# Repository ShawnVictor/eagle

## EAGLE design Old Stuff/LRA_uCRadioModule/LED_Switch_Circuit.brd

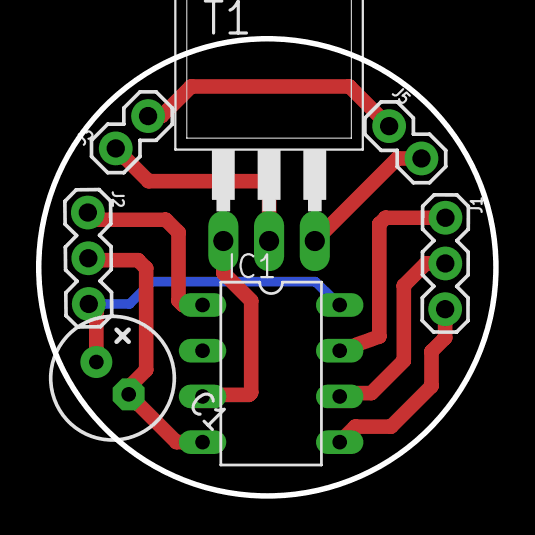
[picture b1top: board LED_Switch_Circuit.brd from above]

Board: 2 copper layers, 25.4 x 25.4 mm, 7 parts (0 on the bottom side), 10 nets.

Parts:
C1: E-025X060
IC1: TINY13-20PU; DIL08
J1, J2: 1X03
J3, J5: 1X02
T1: TIP31; TO220

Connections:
5V: C1.+, IC1.8, J2.3
GND: C1.-, IC1.4, J2.2
unnamed: J5.2, T1.3
unnamed: J3.2, J5.1
unnamed: J3.1, T1.2
unnamed: IC1.3, T1.1
PIN10: IC1.1, J2.1
PIN11: IC1.5, J1.3
PIN12: IC1.6, J1.2
PIN13: IC1.7, J1.1

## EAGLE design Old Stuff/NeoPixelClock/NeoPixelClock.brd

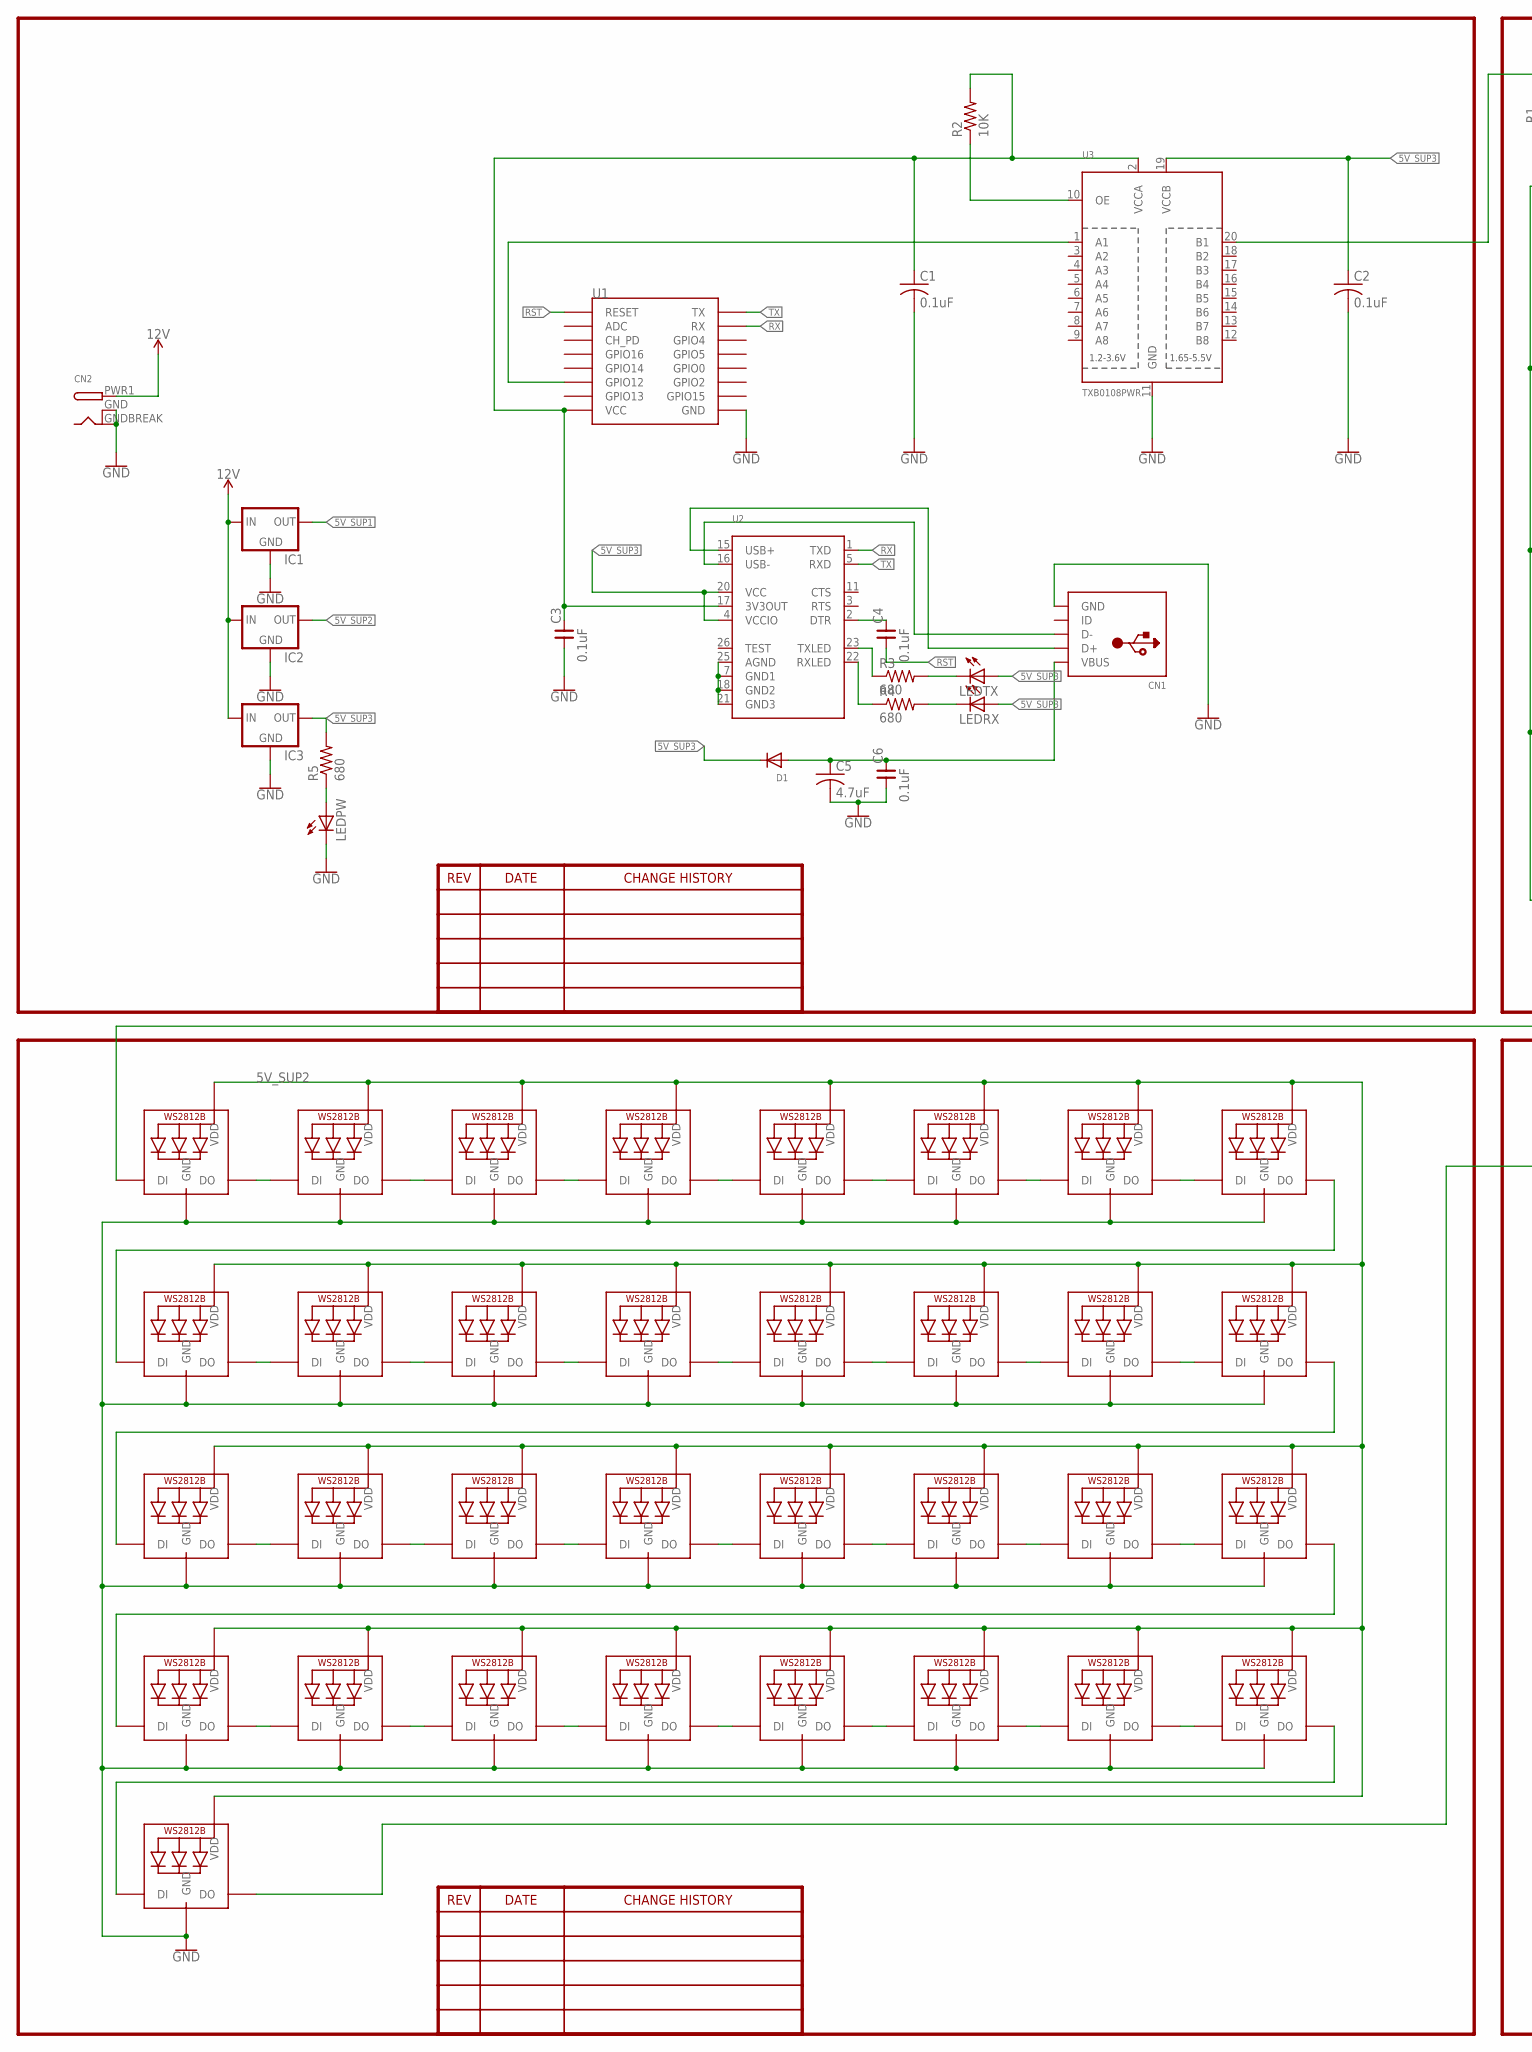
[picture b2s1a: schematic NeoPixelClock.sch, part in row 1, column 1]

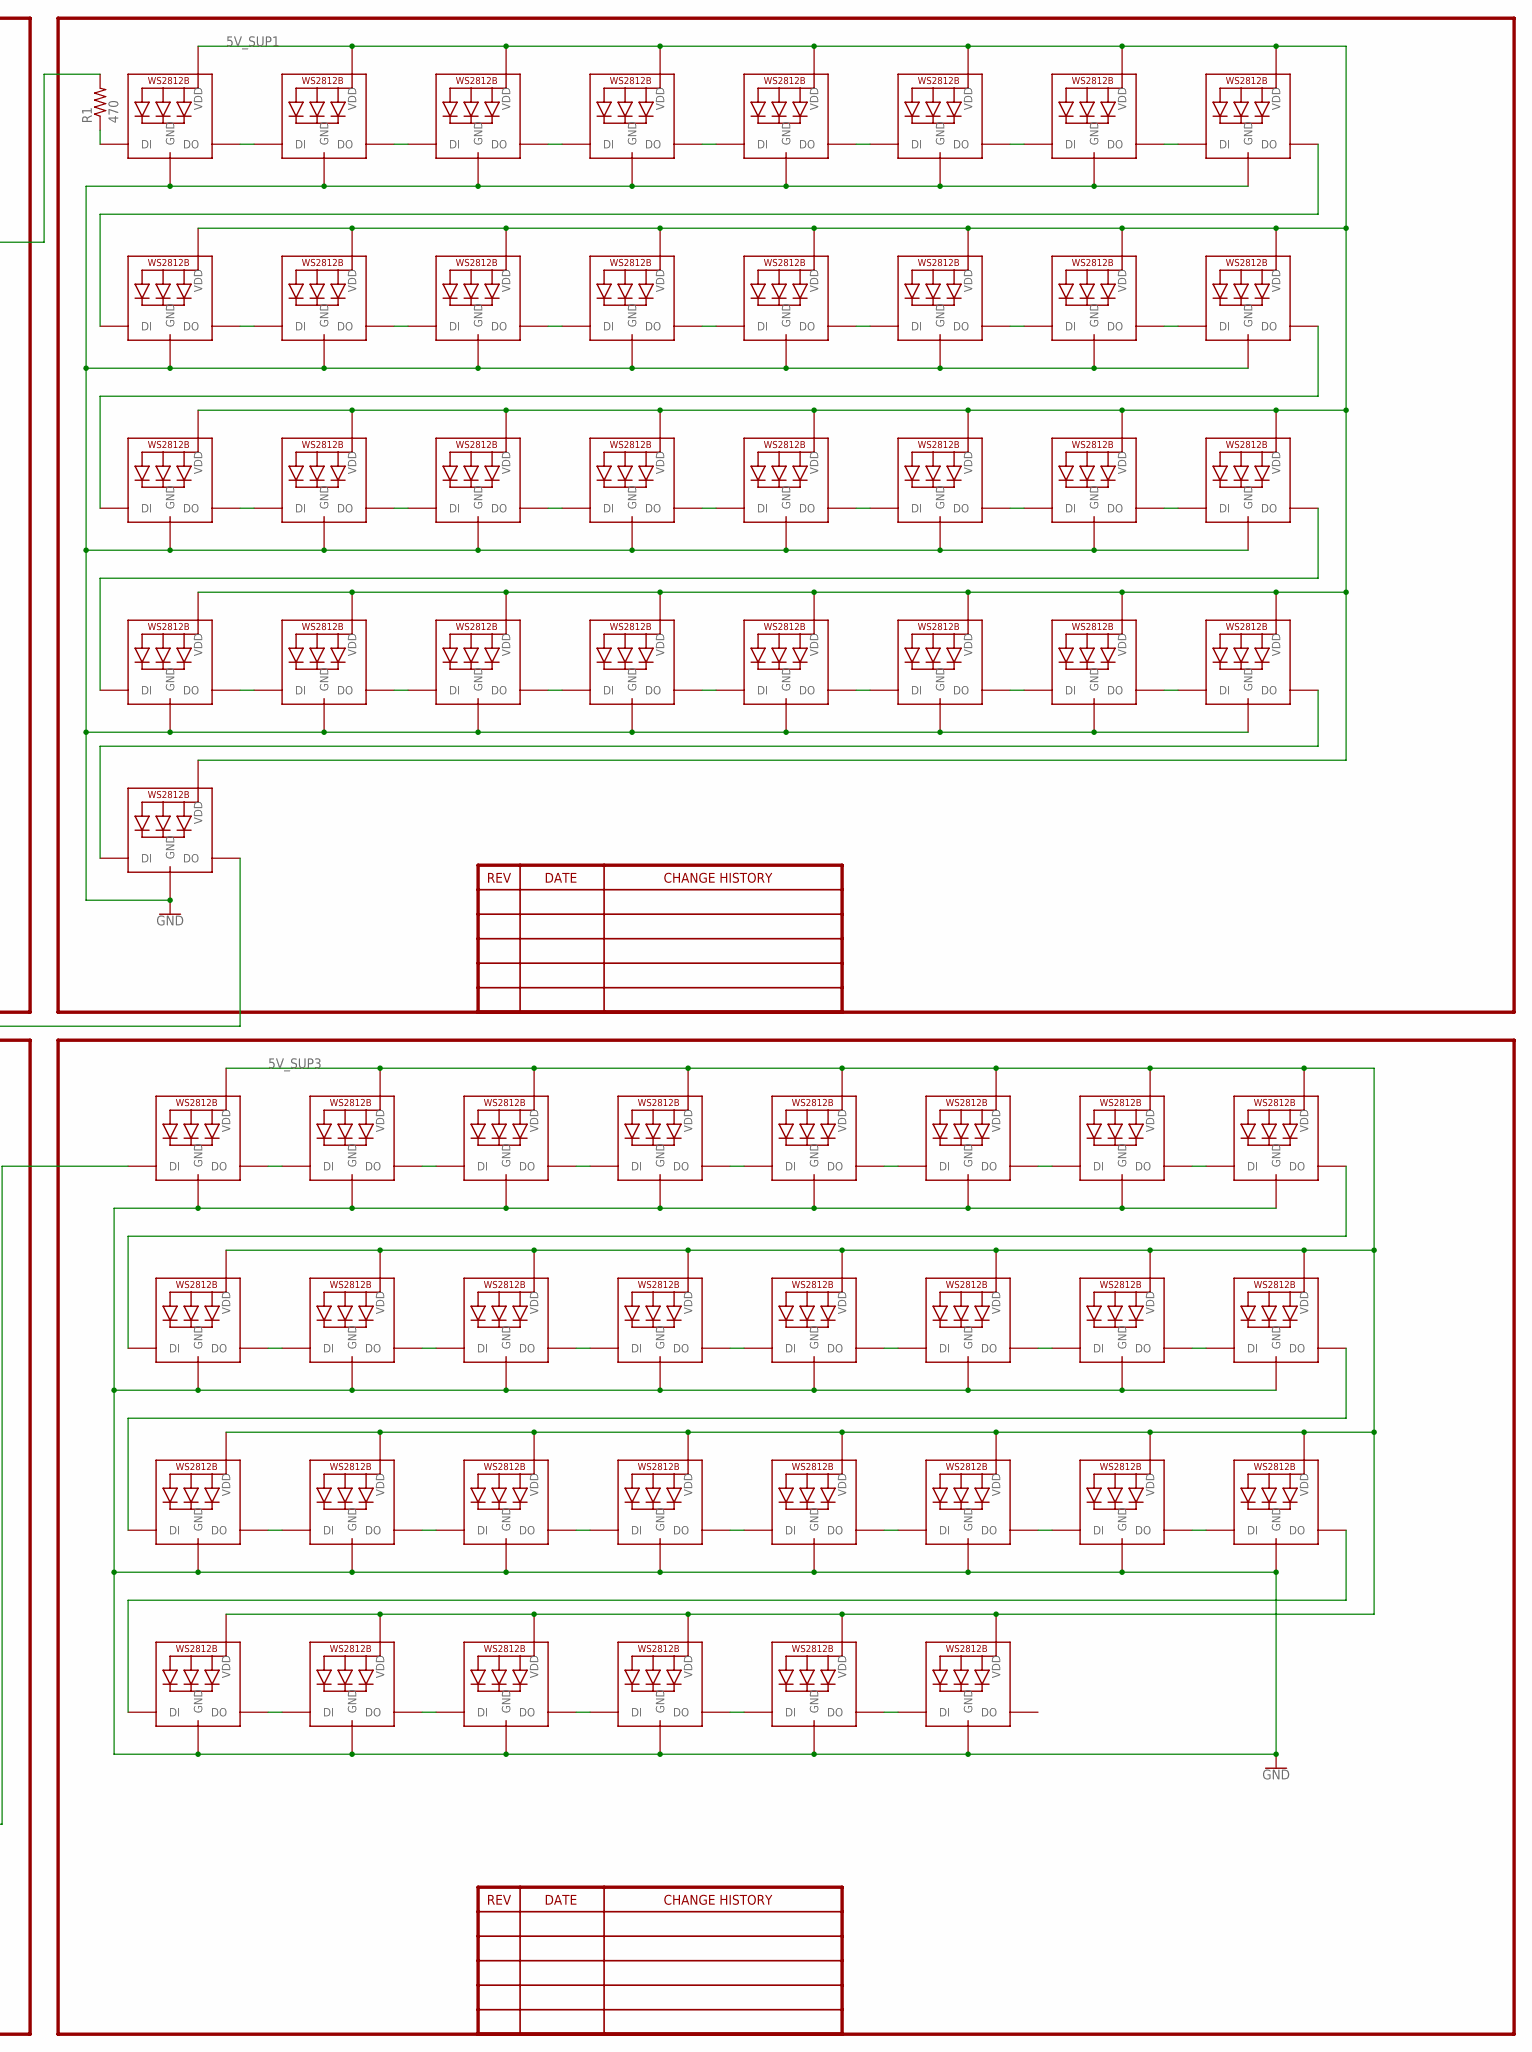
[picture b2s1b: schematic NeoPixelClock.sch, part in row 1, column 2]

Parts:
C1, C2: 0.1uF; C0805
C3, C4, C6: 0.1uF; 0805
C5: 4.7uF; C0805
CN1: USBMINIB; USB-MINIB
CN2: DCBARRELSMT; DCJACK_2MM_SMT
D1: DIODESOD-123; SOD-123
IC1, IC2, IC3: V_REG_78XXSIDE; 78XXL
LED1, LED2, LED3, LED4, LED5, LED6, LED7, LED8, LED9, LED10, LED11, LED12, LED13, LED14, LED15, LED16, LED17, LED18, LED19, LED20, LED21, LED22, LED23, LED24, LED25, LED26, LED27, LED28, LED29, LED30, LED31, LED32, LED33, LED34, LED35, LED36, LED37, LED38, LED39, LED40, LED41, LED42, LED43, LED44, LED45, LED46, LED47, LED48, LED49, LED50, LED51, LED52, LED53, LED54, LED55, LED56, LED57, LED58, LED59, LED60, LED61, LED62, LED63, LED64, LED65, LED66, LED67, LED68, LED69, LED70, LED71, LED72, LED73, LED74, LED75, LED76, LED77, LED78, LED79, LED80, LED81, LED82, LED83, LED84, LED85, LED86, LED87, LED88, LED89, LED90, LED91, LED92, LED93, LED94, LED95, LED96: WS2812B5050; WS2812B
LEDPW: LEDCHIP-LED0805; CHIP-LED0805
LEDRX: LEDCHIP-LED0805; CHIP-LED0805
LEDTX: LEDCHIP-LED0805; CHIP-LED0805
R1: 470; M0805
R2: 10K; R0805
R3, R4, R5: 680; R0805
U1: ESP12
U2: FT232RLSSOP28; SSOP28DB
U3: TXB0108PWR; TSSOP20

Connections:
3V3: C1.1, C3.2, R2.2, U1.VCC, U2.17 (3V3OUT), U3.2 (VCCA)
5V_SUP1: IC1.OUT, LED1.1-VDD (VDD), LED2.1-VDD (VDD), LED3.1-VDD (VDD), LED4.1-VDD (VDD), LED5.1-VDD (VDD), LED6.1-VDD (VDD), LED7.1-VDD (VDD), LED8.1-VDD (VDD), LED9.1-VDD (VDD), LED10.1-VDD (VDD), LED11.1-VDD (VDD), LED12.1-VDD (VDD), LED13.1-VDD (VDD), LED14.1-VDD (VDD), LED15.1-VDD (VDD), LED16.1-VDD (VDD), LED17.1-VDD (VDD), LED18.1-VDD (VDD), LED19.1-VDD (VDD), LED20.1-VDD (VDD), LED21.1-VDD (VDD), LED22.1-VDD (VDD), LED23.1-VDD (VDD), LED24.1-VDD (VDD), LED25.1-VDD (VDD), LED26.1-VDD (VDD), LED27.1-VDD (VDD), LED28.1-VDD (VDD), LED29.1-VDD (VDD), LED30.1-VDD (VDD), LED31.1-VDD (VDD), LED32.1-VDD (VDD), LED33.1-VDD (VDD)
5V_SUP2: IC2.OUT, LED34.1-VDD (VDD), LED35.1-VDD (VDD), LED36.1-VDD (VDD), LED37.1-VDD (VDD), LED38.1-VDD (VDD), LED39.1-VDD (VDD), LED40.1-VDD (VDD), LED41.1-VDD (VDD), LED42.1-VDD (VDD), LED43.1-VDD (VDD), LED44.1-VDD (VDD), LED45.1-VDD (VDD), LED46.1-VDD (VDD), LED47.1-VDD (VDD), LED48.1-VDD (VDD), LED49.1-VDD (VDD), LED50.1-VDD (VDD), LED51.1-VDD (VDD), LED52.1-VDD (VDD), LED53.1-VDD (VDD), LED54.1-VDD (VDD), LED55.1-VDD (VDD), LED56.1-VDD (VDD), LED57.1-VDD (VDD), LED58.1-VDD (VDD), LED59.1-VDD (VDD), LED60.1-VDD (VDD), LED61.1-VDD (VDD), LED62.1-VDD (VDD), LED63.1-VDD (VDD), LED64.1-VDD (VDD), LED65.1-VDD (VDD), LED66.1-VDD (VDD)
5V_SUP3: C2.1, D1.C, IC3.OUT, LED67.1-VDD (VDD), LED68.1-VDD (VDD), LED69.1-VDD (VDD), LED70.1-VDD (VDD), LED71.1-VDD (VDD), LED72.1-VDD (VDD), LED73.1-VDD (VDD), LED74.1-VDD (VDD), LED75.1-VDD (VDD), LED76.1-VDD (VDD), LED77.1-VDD (VDD), LED78.1-VDD (VDD), LED79.1-VDD (VDD), LED80.1-VDD (VDD), LED81.1-VDD (VDD), LED82.1-VDD (VDD), LED83.1-VDD (VDD), LED84.1-VDD (VDD), LED85.1-VDD (VDD), LED86.1-VDD (VDD), LED87.1-VDD (VDD), LED88.1-VDD (VDD), LED89.1-VDD (VDD), LED90.1-VDD (VDD), LED91.1-VDD (VDD), LED92.1-VDD (VDD), LED93.1-VDD (VDD), LED94.1-VDD (VDD), LED95.1-VDD (VDD), LED96.1-VDD (VDD), LEDRX.A, LEDTX.A, R5.2, U2.4 (VCCIO), U2.20 (VCC), U3.19 (VCCB)
12V: CN2.PWR1 (PWR), IC1.IN, IC2.IN, IC3.IN
GND: C1.2, C2.2, C3.1, C5.2, C6.1, CN1.GND, CN2.GND (GNDBREAK), CN2.GNDBREAK (GND), IC1.GND, IC2.GND, IC3.GND, LED1.3-GND (GND), LED2.3-GND (GND), LED3.3-GND (GND), LED4.3-GND (GND), LED5.3-GND (GND), LED6.3-GND (GND), LED7.3-GND (GND), LED8.3-GND (GND), LED9.3-GND (GND), LED10.3-GND (GND), LED11.3-GND (GND), LED12.3-GND (GND), LED13.3-GND (GND), LED14.3-GND (GND), LED15.3-GND (GND), LED16.3-GND (GND), LED17.3-GND (GND), LED18.3-GND (GND), LED19.3-GND (GND), LED20.3-GND (GND), LED21.3-GND (GND), LED22.3-GND (GND), LED23.3-GND (GND), LED24.3-GND (GND), LED25.3-GND (GND), LED26.3-GND (GND), LED27.3-GND (GND), LED28.3-GND (GND), LED29.3-GND (GND), LED30.3-GND (GND), LED31.3-GND (GND), LED32.3-GND (GND), LED33.3-GND (GND), LED34.3-GND (GND), LED35.3-GND (GND), LED36.3-GND (GND), LED37.3-GND (GND), LED38.3-GND (GND), LED39.3-GND (GND), LED40.3-GND (GND), LED41.3-GND (GND), LED42.3-GND (GND), LED43.3-GND (GND), LED44.3-GND (GND), LED45.3-GND (GND), LED46.3-GND (GND), LED47.3-GND (GND), LED48.3-GND (GND), LED49.3-GND (GND), LED50.3-GND (GND), LED51.3-GND (GND), LED52.3-GND (GND), LED53.3-GND (GND), LED54.3-GND (GND), LED55.3-GND (GND), LED56.3-GND (GND), LED57.3-GND (GND), LED58.3-GND (GND), LED59.3-GND (GND), LED60.3-GND (GND), LED61.3-GND (GND), LED62.3-GND (GND), LED63.3-GND (GND), LED64.3-GND (GND), LED65.3-GND (GND), LED66.3-GND (GND), LED67.3-GND (GND), LED68.3-GND (GND), LED69.3-GND (GND), LED70.3-GND (GND), LED71.3-GND (GND), LED72.3-GND (GND), LED73.3-GND (GND), LED74.3-GND (GND), LED75.3-GND (GND), LED76.3-GND (GND), LED77.3-GND (GND), LED78.3-GND (GND), LED79.3-GND (GND), LED80.3-GND (GND), LED81.3-GND (GND), LED82.3-GND (GND), LED83.3-GND (GND), LED84.3-GND (GND), LED85.3-GND (GND), LED86.3-GND (GND), LED87.3-GND (GND), LED88.3-GND (GND), LED89.3-GND (GND), LED90.3-GND (GND), LED91.3-GND (GND), LED92.3-GND (GND), LED93.3-GND (GND), LED94.3-GND (GND), LED95.3-GND (GND), LED96.3-GND (GND), LEDPW.C, U1.GND, U3.11 (GND)
unnamed: U1.GPIO12, U3.1 (A1)
unnamed: LED34.2-DOUT (DO), LED35.4-DIN (DI)
unnamed: LED35.2-DOUT (DO), LED36.4-DIN (DI)
unnamed: R1.2, U3.20 (B1)
unnamed: LED1.2-DOUT (DO), LED2.4-DIN (DI)
unnamed: LED2.2-DOUT (DO), LED3.4-DIN (DI)
unnamed: LED3.2-DOUT (DO), LED4.4-DIN (DI)
unnamed: LED4.2-DOUT (DO), LED5.4-DIN (DI)
unnamed: LED5.2-DOUT (DO), LED6.4-DIN (DI)
unnamed: LED6.2-DOUT (DO), LED7.4-DIN (DI)
unnamed: LED7.2-DOUT (DO), LED8.4-DIN (DI)
unnamed: U2.7 (GND1), U2.18 (GND2), U2.21 (GND3), U2.25 (AGND)
unnamed: LED8.2-DOUT (DO), LED9.4-DIN (DI)
unnamed: LED9.2-DOUT (DO), LED10.4-DIN (DI)
unnamed: LED10.2-DOUT (DO), LED11.4-DIN (DI)
unnamed: LED11.2-DOUT (DO), LED12.4-DIN (DI)
unnamed: LED12.2-DOUT (DO), LED13.4-DIN (DI)
unnamed: LED13.2-DOUT (DO), LED14.4-DIN (DI)
unnamed: LED14.2-DOUT (DO), LED15.4-DIN (DI)
unnamed: LED15.2-DOUT (DO), LED16.4-DIN (DI)
unnamed: LED16.2-DOUT (DO), LED17.4-DIN (DI)
unnamed: LED17.2-DOUT (DO), LED18.4-DIN (DI)
unnamed: LED18.2-DOUT (DO), LED19.4-DIN (DI)
unnamed: LED19.2-DOUT (DO), LED20.4-DIN (DI)
unnamed: LED20.2-DOUT (DO), LED21.4-DIN (DI)
unnamed: LED21.2-DOUT (DO), LED22.4-DIN (DI)
unnamed: LED22.2-DOUT (DO), LED23.4-DIN (DI)
unnamed: LED23.2-DOUT (DO), LED24.4-DIN (DI)
unnamed: LED24.2-DOUT (DO), LED25.4-DIN (DI)
unnamed: LED25.2-DOUT (DO), LED26.4-DIN (DI)
unnamed: LED26.2-DOUT (DO), LED27.4-DIN (DI)
unnamed: LED27.2-DOUT (DO), LED28.4-DIN (DI)
unnamed: LED28.2-DOUT (DO), LED29.4-DIN (DI)
unnamed: LED29.2-DOUT (DO), LED30.4-DIN (DI)
unnamed: LED30.2-DOUT (DO), LED31.4-DIN (DI)
unnamed: LED31.2-DOUT (DO), LED32.4-DIN (DI)
unnamed: LED32.2-DOUT (DO), LED33.4-DIN (DI)
unnamed: LED36.2-DOUT (DO), LED37.4-DIN (DI)
unnamed: LED37.2-DOUT (DO), LED38.4-DIN (DI)
unnamed: LED38.2-DOUT (DO), LED39.4-DIN (DI)
unnamed: LED39.2-DOUT (DO), LED40.4-DIN (DI)
unnamed: LED40.2-DOUT (DO), LED41.4-DIN (DI)
unnamed: C5.1, C6.2, CN1.VBUS, D1.A
unnamed: LED41.2-DOUT (DO), LED42.4-DIN (DI)
unnamed: LED42.2-DOUT (DO), LED43.4-DIN (DI)
unnamed: LED43.2-DOUT (DO), LED44.4-DIN (DI)
unnamed: LED44.2-DOUT (DO), LED45.4-DIN (DI)
unnamed: LED45.2-DOUT (DO), LED46.4-DIN (DI)
unnamed: LED46.2-DOUT (DO), LED47.4-DIN (DI)
unnamed: LED47.2-DOUT (DO), LED48.4-DIN (DI)
unnamed: LED48.2-DOUT (DO), LED49.4-DIN (DI)
unnamed: LED49.2-DOUT (DO), LED50.4-DIN (DI)
unnamed: LED50.2-DOUT (DO), LED51.4-DIN (DI)
unnamed: LED51.2-DOUT (DO), LED52.4-DIN (DI)
unnamed: LED52.2-DOUT (DO), LED53.4-DIN (DI)
unnamed: LED53.2-DOUT (DO), LED54.4-DIN (DI)
unnamed: LED54.2-DOUT (DO), LED55.4-DIN (DI)
unnamed: LED55.2-DOUT (DO), LED56.4-DIN (DI)
unnamed: LED56.2-DOUT (DO), LED57.4-DIN (DI)
unnamed: LED57.2-DOUT (DO), LED58.4-DIN (DI)
unnamed: LED58.2-DOUT (DO), LED59.4-DIN (DI)
unnamed: LED59.2-DOUT (DO), LED60.4-DIN (DI)
unnamed: LED60.2-DOUT (DO), LED61.4-DIN (DI)
unnamed: LED61.2-DOUT (DO), LED62.4-DIN (DI)
unnamed: LED62.2-DOUT (DO), LED63.4-DIN (DI)
unnamed: LED63.2-DOUT (DO), LED64.4-DIN (DI)
unnamed: LED64.2-DOUT (DO), LED65.4-DIN (DI)
unnamed: LED65.2-DOUT (DO), LED66.4-DIN (DI)
unnamed: CN1.D-, U2.16 (USB-)
unnamed: LED67.2-DOUT (DO), LED68.4-DIN (DI)
unnamed: LED68.2-DOUT (DO), LED69.4-DIN (DI)
unnamed: LED69.2-DOUT (DO), LED70.4-DIN (DI)
unnamed: LED70.2-DOUT (DO), LED71.4-DIN (DI)
unnamed: LED71.2-DOUT (DO), LED72.4-DIN (DI)
unnamed: LED72.2-DOUT (DO), LED73.4-DIN (DI)
unnamed: LED73.2-DOUT (DO), LED74.4-DIN (DI)
unnamed: CN1.D+, U2.15 (USB+)
unnamed: LED74.2-DOUT (DO), LED75.4-DIN (DI)
unnamed: LED75.2-DOUT (DO), LED76.4-DIN (DI)
unnamed: LED76.2-DOUT (DO), LED77.4-DIN (DI)
unnamed: LED77.2-DOUT (DO), LED78.4-DIN (DI)
unnamed: LED78.2-DOUT (DO), LED79.4-DIN (DI)
unnamed: LED79.2-DOUT (DO), LED80.4-DIN (DI)
unnamed: LED80.2-DOUT (DO), LED81.4-DIN (DI)
unnamed: LED81.2-DOUT (DO), LED82.4-DIN (DI)
unnamed: LED82.2-DOUT (DO), LED83.4-DIN (DI)
unnamed: LED83.2-DOUT (DO), LED84.4-DIN (DI)
unnamed: LED84.2-DOUT (DO), LED85.4-DIN (DI)
unnamed: LED85.2-DOUT (DO), LED86.4-DIN (DI)
unnamed: LED86.2-DOUT (DO), LED87.4-DIN (DI)
unnamed: LED87.2-DOUT (DO), LED88.4-DIN (DI)
unnamed: LED88.2-DOUT (DO), LED89.4-DIN (DI)
unnamed: LED89.2-DOUT (DO), LED90.4-DIN (DI)
unnamed: LED90.2-DOUT (DO), LED91.4-DIN (DI)
unnamed: LED91.2-DOUT (DO), LED92.4-DIN (DI)
unnamed: LED92.2-DOUT (DO), LED93.4-DIN (DI)
unnamed: LED93.2-DOUT (DO), LED94.4-DIN (DI)
unnamed: LED94.2-DOUT (DO), LED95.4-DIN (DI)
unnamed: LED95.2-DOUT (DO), LED96.4-DIN (DI)
unnamed: LED1.4-DIN (DI), R1.1
unnamed: LED33.2-DOUT (DO), LED34.4-DIN (DI)
unnamed: LED66.2-DOUT (DO), LED67.4-DIN (DI)
unnamed: LEDTX.C, R3.2
unnamed: C4.2, U2.2 (DTR)
unnamed: R3.1, U2.23 (TXLED)
unnamed: R4.1, U2.22 (RXLED)
unnamed: LEDRX.C, R4.2
unnamed: LEDPW.A, R5.1
unnamed: R2.1, U3.10 (OE)
RST: C4.1, U1.RESET
RX: U1.RX, U2.1 (TXD)
TX: U1.TX, U2.5 (RXD)

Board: 2 copper layers, 119 parts (0 on the bottom side), 118 nets, no tracks yet.

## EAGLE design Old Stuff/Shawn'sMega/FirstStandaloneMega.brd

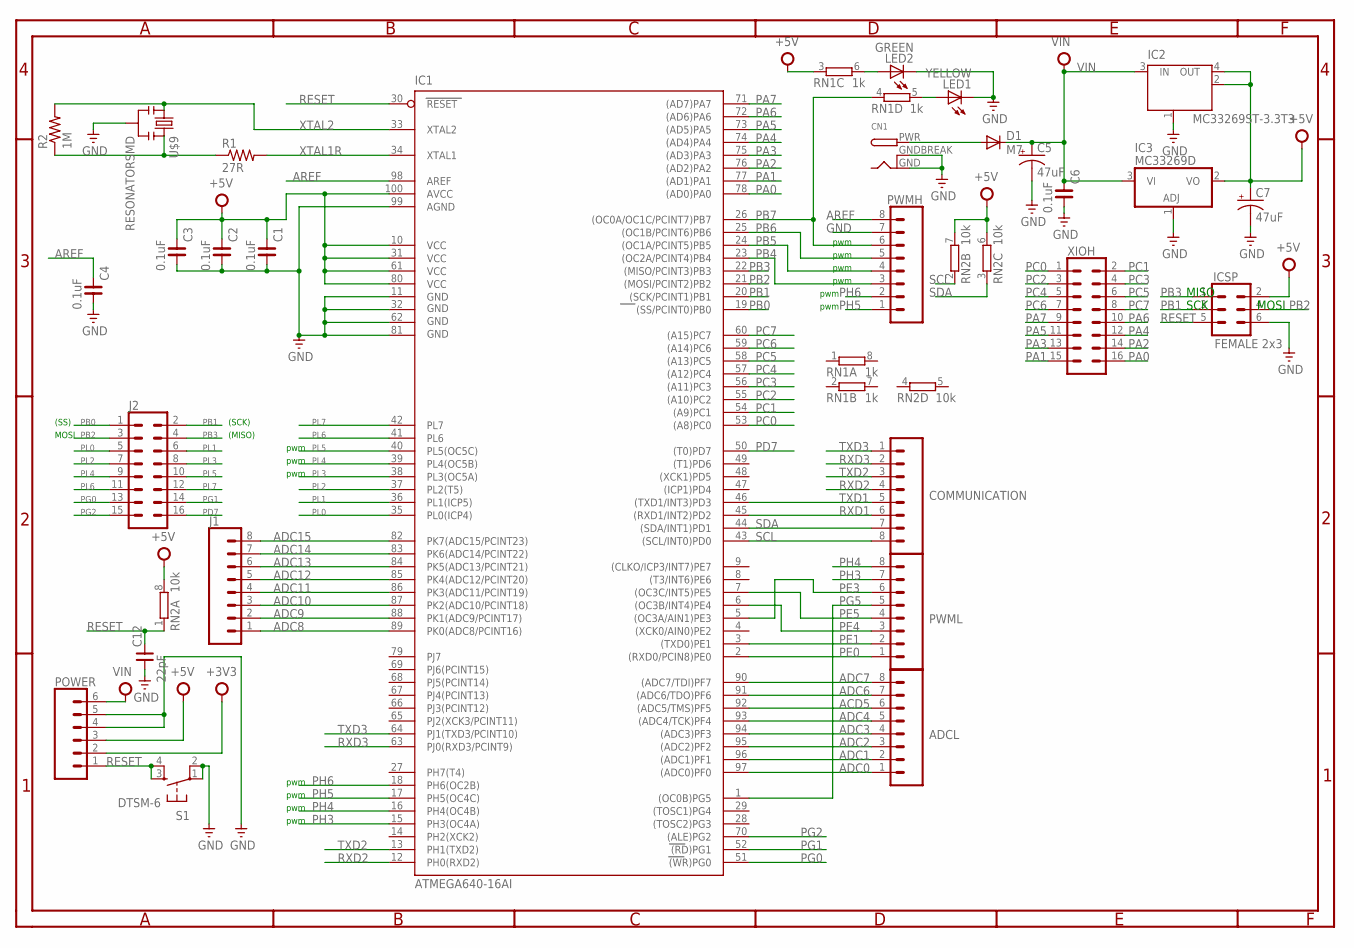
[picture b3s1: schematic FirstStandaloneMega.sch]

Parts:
ADCL: CONN_08"; 1X08
C1, C2, C3, C4, C6: 0.1uF; C0805
C5, C7: 47uF; PANASONIC_D
C12: 22pF; 0805
CN1: DCBARRELPTH; DCJACK_2MM_PTH
COMMUNICATION: CONN_08"; 1X08
D1: M7; SMB
IC1: ATMEGA640-16AI; TQFP100
IC2: MC33269ST-3.3T3; SOT223
IC3: MC33269D; DPACK
ICSP: FEMALE 2x3; 2X3
J1: CONN_08"; 1X08
J2: CONN_08X2; 2X8
LED1: YELLOW; CHIPLED_0805
LED2: GREEN; CHIPLED_0805
POWER: CONN_06SILK_FEMALE_PTH; 1X06
PWMH: CONN_08"; 1X08
PWML: CONN_08"; 1X08
R1: 27R; R0805
R2: 1M; R0805
RN1: 1k; CAY16
RN2: 10k; CAY16
S1: DTSM-6
U$9: RESONATORSMD; RESONATOR-SMD
XIOH: CONN_08X2; 2X8

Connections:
+3V3: POWER.2
+5V: C1.2, C2.2, C3.2, C7.+, IC1.10 (VCC), IC1.31 (VCC1), IC1.61 (VCC2), IC1.80 (VCC3), IC1.100 (AVCC), IC2.2 (OUT), IC2.4 (OUT), IC3.2 (VO), ICSP.2, POWER.3, RN1.3 (1), RN2.6 (2), RN2.7 (2), RN2.8 (2)
ACD5: ADCL.6, IC1.92 ((ADC5/TMS)PF5)
ADC0: ADCL.1, IC1.97 ((ADC0)PF0)
ADC1: ADCL.2, IC1.96 ((ADC1)PF1)
ADC2: ADCL.3, IC1.95 ((ADC2)PF2)
ADC3: ADCL.4, IC1.94 ((ADC3)PF3)
ADC4: ADCL.5, IC1.93 ((ADC4/TCK)PF4)
ADC6: ADCL.7, IC1.91 ((ADC6/TDO)PF6)
ADC7: ADCL.8, IC1.90 ((ADC7/TDI)PF7)
ADC8: IC1.89 (PK0(ADC8/PCINT16)), J1.1
ADC9: IC1.88 (PK1(ADC9/PCINT17)), J1.2
ADC10: IC1.87 (PK2(ADC10/PCINT18)), J1.3
ADC11: IC1.86 (PK3(ADC11/PCINT19)), J1.4
ADC12: IC1.85 (PK4(ADC12/PCINT20)), J1.5
ADC13: IC1.84 (PK5(ADC13/PCINT21)), J1.6
ADC14: IC1.83 (PK6(ADC14/PCINT22)), J1.7
ADC15: IC1.82 (PK7(ADC15/PCINT23)), J1.8
AREF: C4.2, IC1.98 (AREF), PWMH.8
GND: C1.1, C2.1, C3.1, C4.1, C5.-, C6.1, C7.-, C12.1, CN1.GND, CN1.GNDBREAK, IC1.11 (GND), IC1.32 (GND1), IC1.62 (GND2), IC1.81 (GND3), IC1.99 (AGND), IC2.1 (GND/ADJ), IC3.1 (ADJ), ICSP.6, LED1.C, LED2.C, POWER.4, POWER.5, PWMH.7, S1.1, S1.2, U$9.2
unnamed: R1.1, R2.1, U$9.3
unnamed: LED1.A, RN1.5 (2)
unnamed: CN1.PWR, D1.A
unnamed: LED2.A, RN1.6 (2)
PA0: IC1.78 ((AD0)PA0), XIOH.16
PA1: IC1.77 ((AD1)PA1), XIOH.15
PA2: IC1.76 ((AD2)PA2), XIOH.14
PA3: IC1.75 ((AD3)PA3), XIOH.13
PA4: IC1.74 ((AD4)PA4), XIOH.12
PA5: IC1.73 ((AD5)PA5), XIOH.11
PA6: IC1.72 ((AD6)PA6), XIOH.10
PA7: IC1.71 ((AD7)PA7), XIOH.9
PB0: IC1.19 ((SS/PCINT0)PB0), J2.1
PB1: IC1.20 ((SCK/PCINT1)PB1), ICSP.3, J2.2
PB2: IC1.21 ((MOSI/PCINT2)PB2), ICSP.4, J2.3
PB3: IC1.22 ((MISO/PCINT3)PB3), ICSP.1, J2.4
PB4: IC1.23 ((OC2A/PCINT4)PB4), PWMH.3
PB5: IC1.24 ((OC1A/PCINT5)PB5), PWMH.4
PB6: IC1.25 ((OC1B/PCINT6)PB6), PWMH.5
PB7: IC1.26 ((OC0A/OC1C/PCINT7)PB7), PWMH.6, RN1.4 (1)
PC0: IC1.53 ((A8)PC0), XIOH.1
PC1: IC1.54 ((A9)PC1), XIOH.2
PC2: IC1.55 ((A10)PC2), XIOH.3
PC3: IC1.56 ((A11)PC3), XIOH.4
PC4: IC1.57 ((A12)PC4), XIOH.5
PC5: IC1.58 ((A13)PC5), XIOH.6
PC6: IC1.59 ((A14)PC6), XIOH.7
PC7: IC1.60 ((A15)PC7), XIOH.8
PD7: IC1.50 ((T0)PD7), J2.16
PE0: IC1.2 ((RXD0/PCIN8)PE0), PWML.1
PE1: IC1.3 ((TXD0)PE1), PWML.2
PE3: IC1.5 ((OC3A/AIN1)PE3), PWML.6
PE4: IC1.6 ((OC3B/INT4)PE4), PWML.3
PE5: IC1.7 ((OC3C/INT5)PE5), PWML.4
PG0: IC1.51 ((WR)PG0), J2.13
PG1: IC1.52 ((RD)PG1), J2.14
PG2: IC1.70 ((ALE)PG2), J2.15
PG5: IC1.1 ((OC0B)PG5), PWML.5
PH3: IC1.15 (PH3(OC4A)), PWML.7
PH4: IC1.16 (PH4(OC4B)), PWML.8
PH5: IC1.17 (PH5(OC4C)), PWMH.1
PH6: IC1.18 (PH6(OC2B)), PWMH.2
PL0: IC1.35 (PL0(ICP4)), J2.5
PL1: IC1.36 (PL1(ICP5)), J2.6
PL2: IC1.37 (PL2(T5)), J2.7
PL3: IC1.38 (PL3(OC5A)), J2.8
PL4: IC1.39 (PL4(OC5B)), J2.9
PL5: IC1.40 (PL5(OC5C)), J2.10
PL6: IC1.41 (PL6), J2.11
PL7: IC1.42 (PL7), J2.12
RESET: C12.2, IC1.30 (RESET), ICSP.5, POWER.1, RN2.1, S1.3, S1.4
RXD1: COMMUNICATION.6, IC1.45 ((RXD1/INT2)PD2)
RXD2: COMMUNICATION.4, IC1.12 (PH0(RXD2))
RXD3: COMMUNICATION.2, IC1.63 (PJ0(RXD3/PCINT9))
SCL: COMMUNICATION.8, IC1.43 ((SCL/INT0)PD0), RN2.2 (1)
SDA: COMMUNICATION.7, IC1.44 ((SDA/INT1)PD1), RN2.3 (1)
TXD1: COMMUNICATION.5, IC1.46 ((TXD1/INT3)PD3)
TXD2: COMMUNICATION.3, IC1.13 (PH1(TXD2))
TXD3: COMMUNICATION.1, IC1.64 (PJ1(TXD3/PCINT10))
VIN: C5.+, C6.2, D1.C, IC2.3 (IN), IC3.3 (VI), POWER.6
XTAL1R: IC1.34 (XTAL1), R1.2
XTAL2: IC1.33 (XTAL2), R2.2, U$9.1

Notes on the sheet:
pwm
(SS)
MOSI
(SCK)
(MISO)
MISO
SCK

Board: 2 copper layers, 30 parts (0 on the bottom side), 81 nets, no tracks yet.

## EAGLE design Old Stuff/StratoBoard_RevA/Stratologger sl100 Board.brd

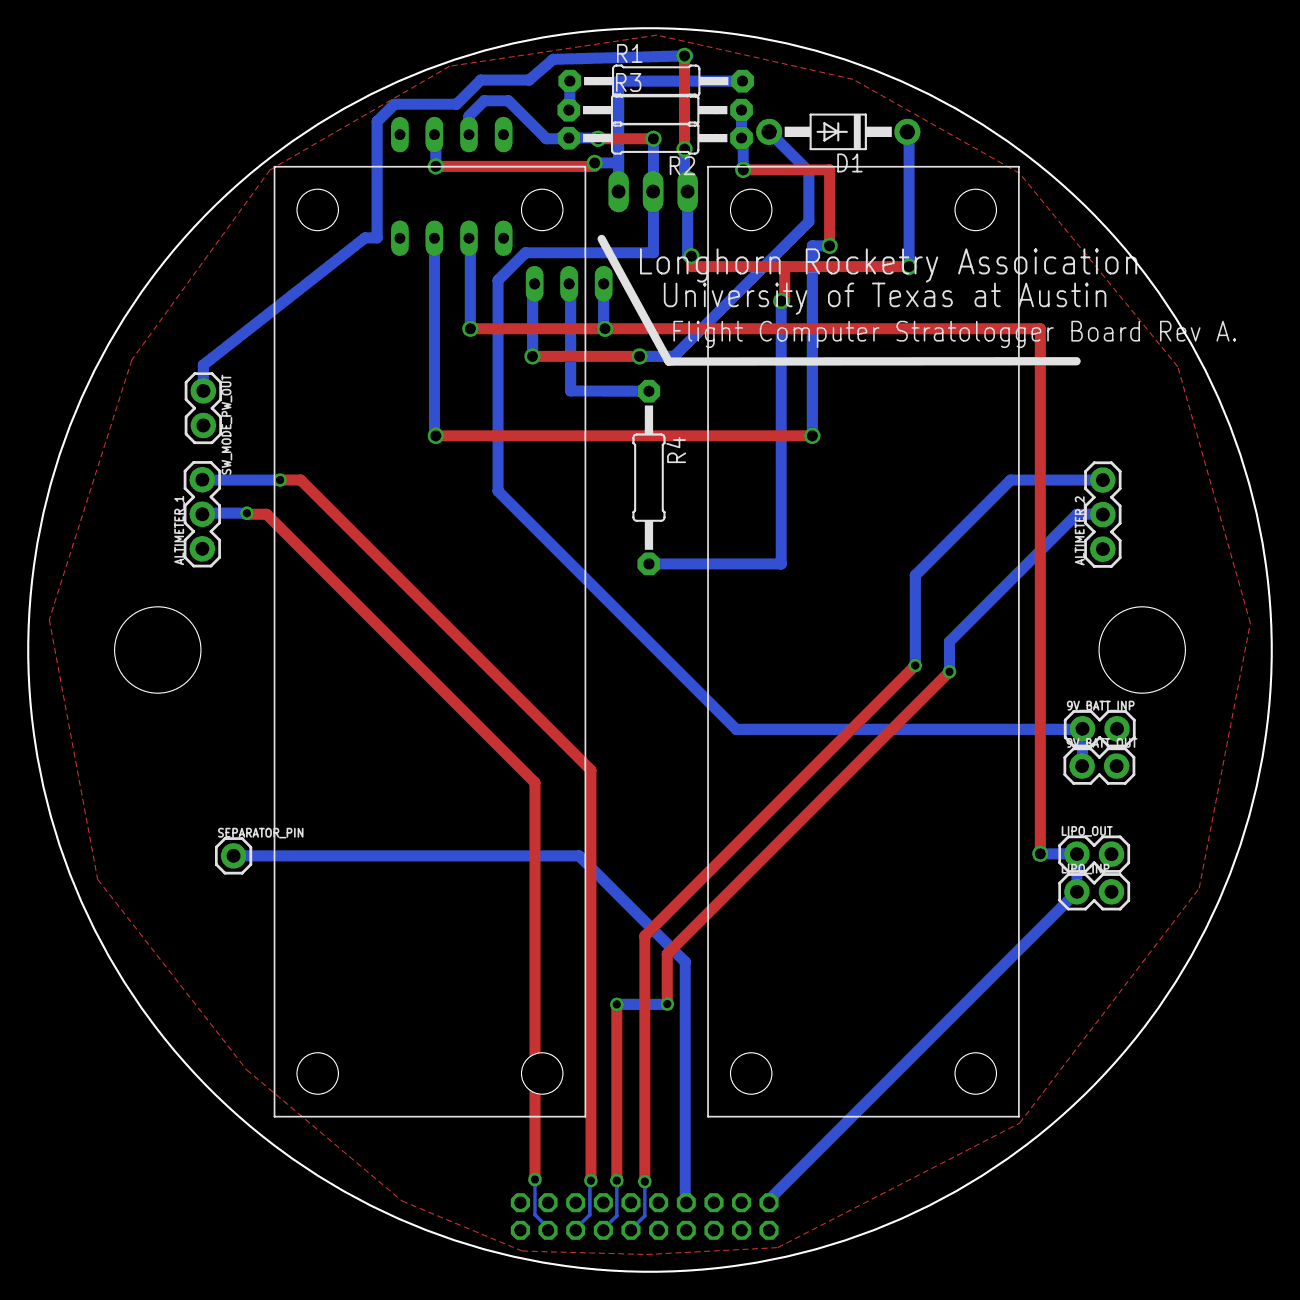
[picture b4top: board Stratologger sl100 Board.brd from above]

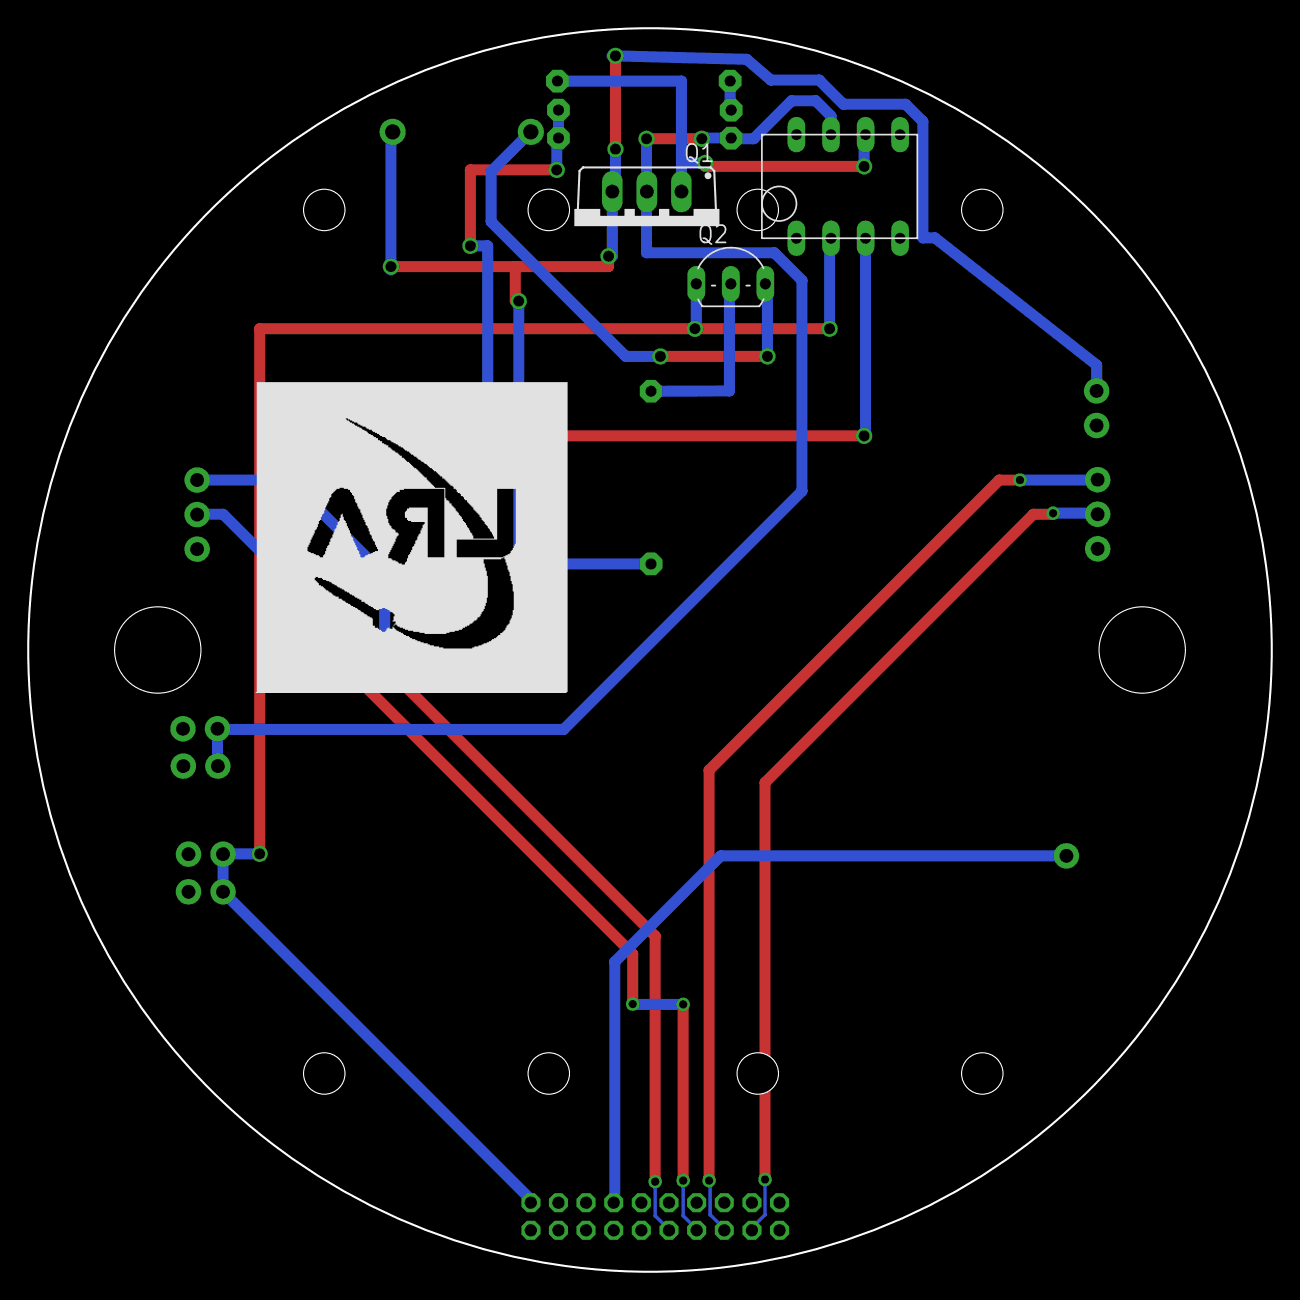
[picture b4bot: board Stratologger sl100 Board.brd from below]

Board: 2 copper layers, 91.4 x 91.4 mm, 19 parts (3 on the bottom side), 13 nets.

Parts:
9V_BATT_INP, 9V_BATT_OUT: 1X02
ALTIMETER_1, ALTIMETER_2: 1X03
D1: 1N4004; DO41-10
LIPO_INP: 1X02
LIPO_OUT: 1X02
Q1: BUZ11BV; TO220BV
Q2: 2N2907; TO92-EBC-OVAL
R1: 10k; 0207/12
R2: 100; 0207/12
R3: 125; 0207/12
R4: 1k; 0207/12
SEPARATOR_PIN: 1X01
SW_MODE_PW_OUT: 1X02
U$1: LM471; LM741
U$2, U$4: STRATOLOGGER
U$3: SMALLHEADERPACKAGE

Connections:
5V_DIV: R2.1, R3.2, U$1.LN+
9V: 9V_BATT_INP.1, 9V_BATT_OUT.1, Q1.D, R2.2, U$1.VCC+
D1: SEPARATOR_PIN.1, U$3.P$13
GND: 9V_BATT_INP.2, 9V_BATT_OUT.2, ALTIMETER_1.1, ALTIMETER_2.1, LIPO_INP.2, LIPO_OUT.2, R1.1, R3.1, SW_MODE_PW_OUT.2, U$1.VCC-, U$3.P$20
LIPO_BATT: LIPO_INP.1, LIPO_OUT.1, Q2.E, U$1.LN-, U$3.P$19
unnamed: Q2.B, R4.1
unnamed: D1.A, Q2.C
unnamed: Q1.G, R1.2, U$1.OUT
unnamed: D1.C, Q1.S, R4.2, SW_MODE_PW_OUT.1
RX1: ALTIMETER_1.2, U$3.P$7
RX2: ALTIMETER_2.2, U$3.P$9
TX1: ALTIMETER_1.3, U$3.P$8
TX2: ALTIMETER_2.3, U$3.P$10

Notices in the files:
parts and their libraries:
SparkFun-Connectors: Licensing: Creative Commons ShareAlike 4.0 International - https://creativecommons.org/licenses/by-sa/4.0
dframes: Copyright (C) 2004, Bob Starr (bobstarr@mindspring.com)
rc-master: Copyright (C) 2007, Bob Starr
con-jst-ph: Copyright (C) 2016, Bob Starr
